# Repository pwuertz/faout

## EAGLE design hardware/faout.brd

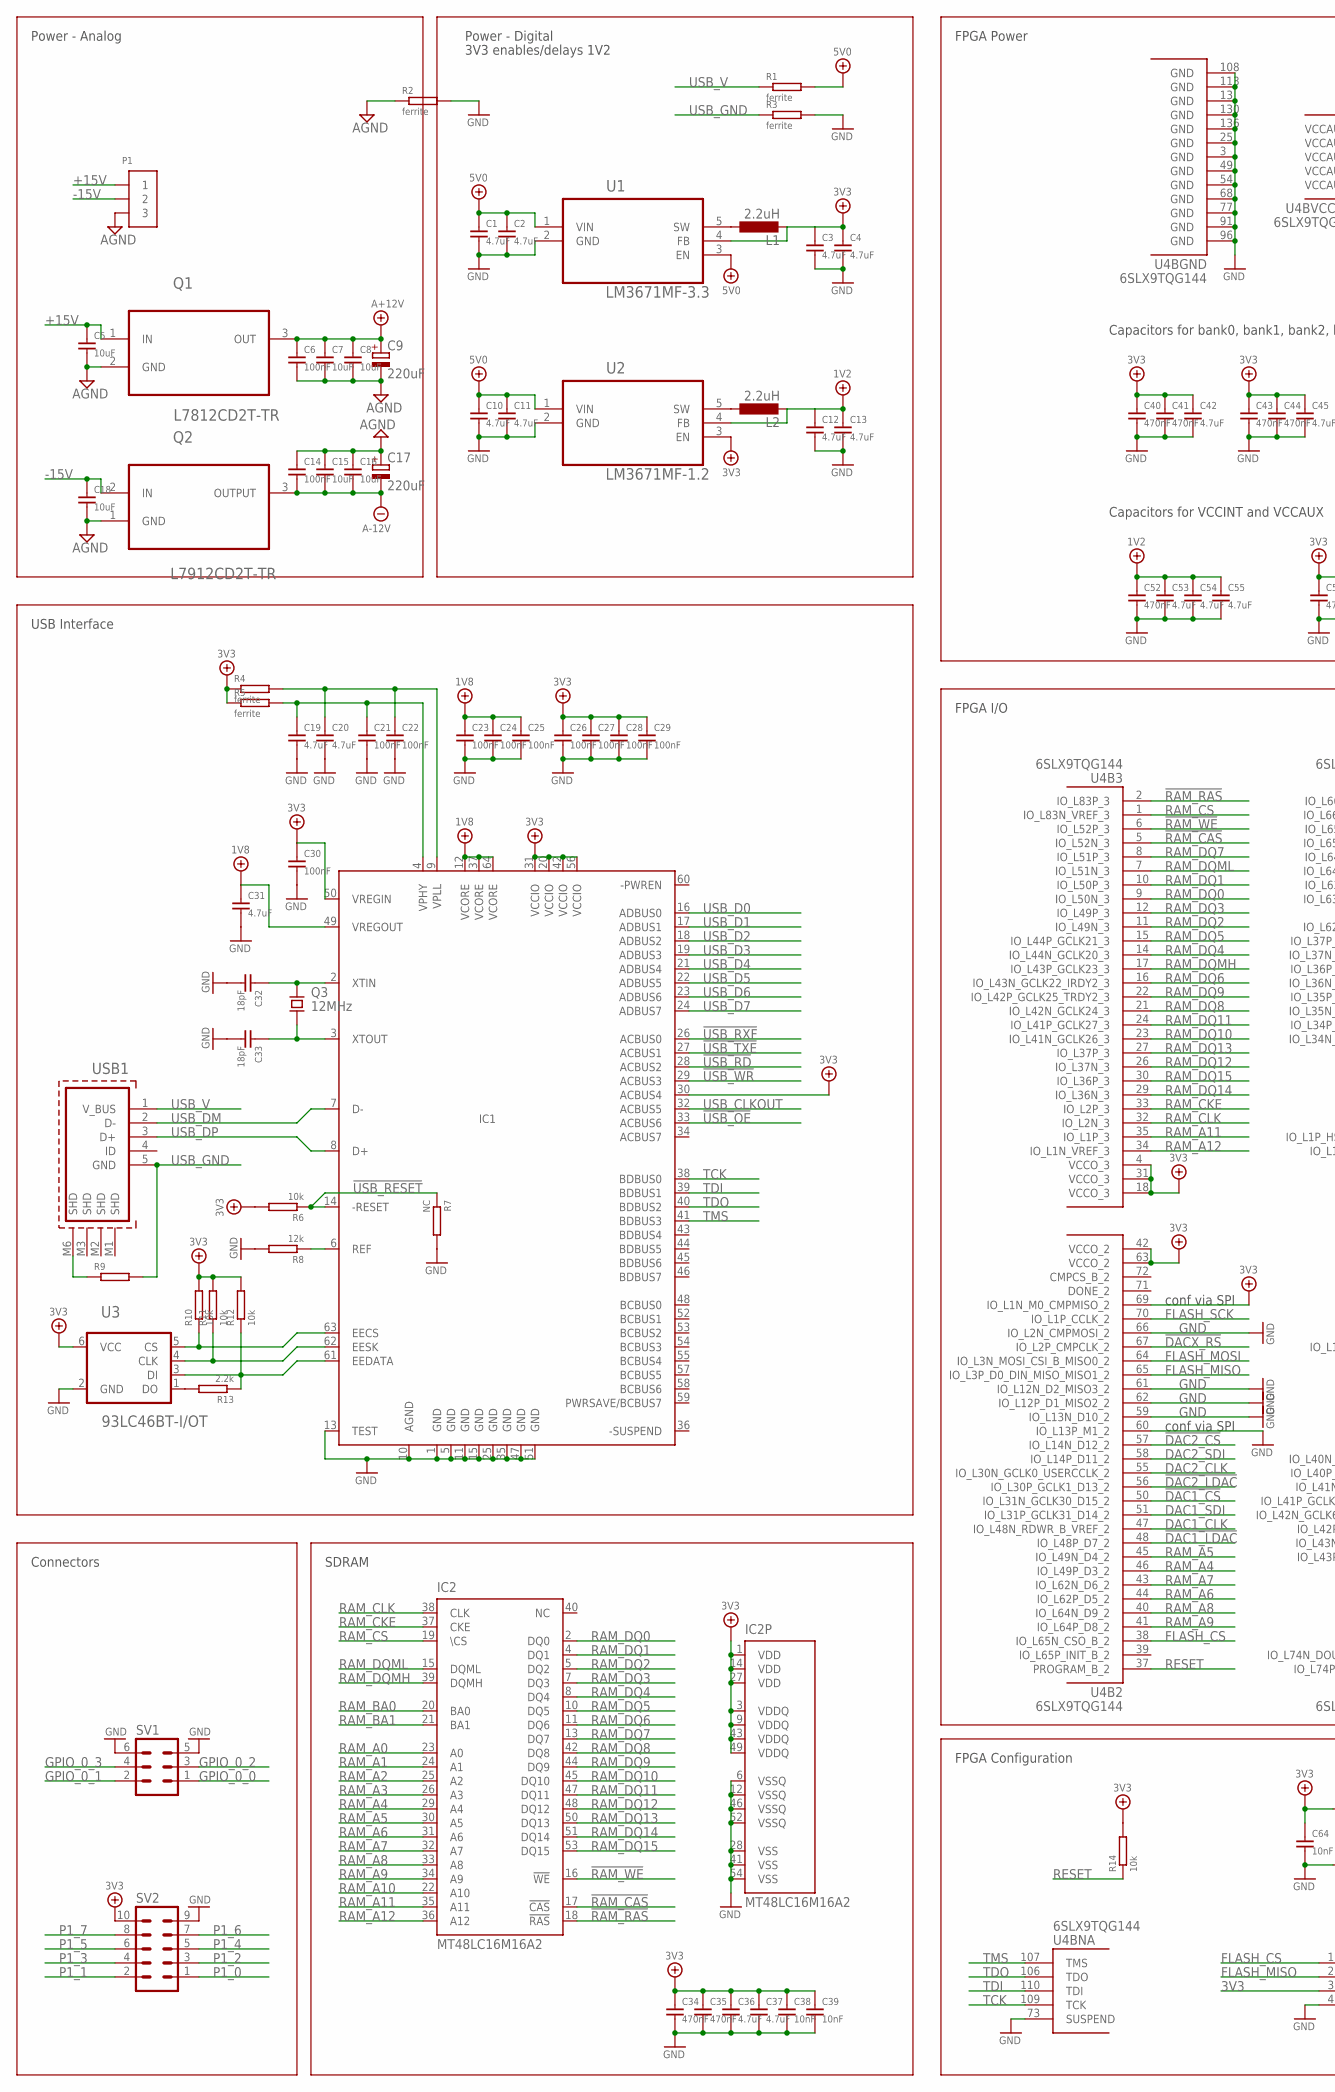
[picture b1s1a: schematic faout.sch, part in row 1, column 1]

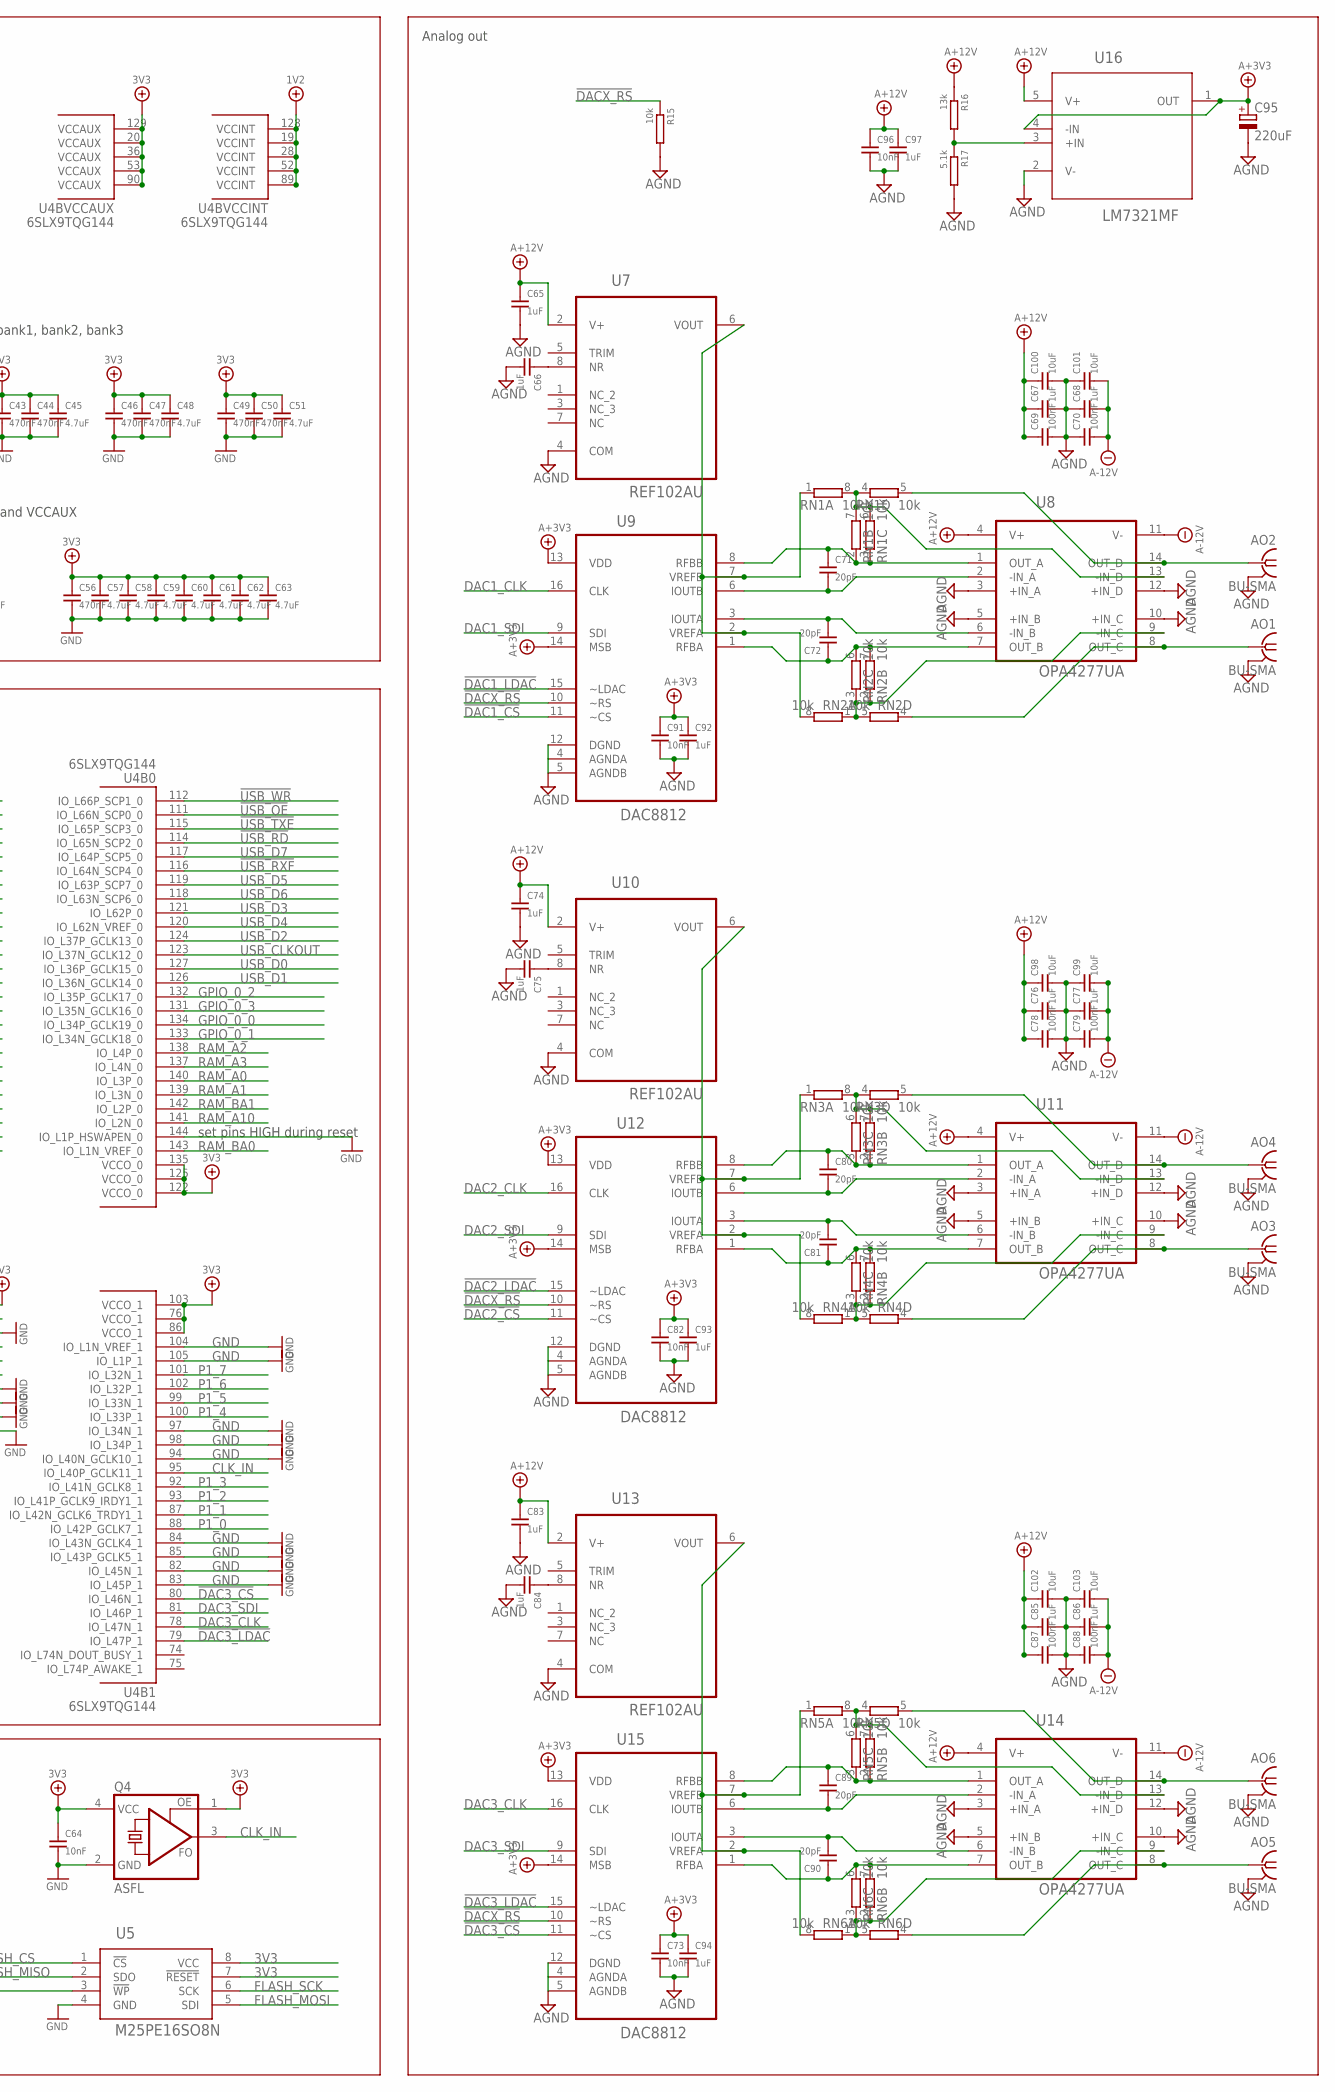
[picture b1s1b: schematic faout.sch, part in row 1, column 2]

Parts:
AO1, AO2, AO3, AO4, AO5, AO6: BU-SMA; BU-SMA-H
C1, C2, C3, C4, C10, C11, C12, C13, C19, C20, C31, C36, C37, C42, C45, C48, C51, C53, C54, C55, C57, C58, C59, C60, C61, C62, C63: 4.7uF; R0603
C5, C7, C8, C15, C16, C18, C98, C99, C100, C101, C102, C103: 10uF; R0805
C6, C14, C21, C22, C23, C24, C25, C26, C27, C28, C29, C30, C69, C70, C78, C79, C87, C88: 100nF; R0603
C9, C17, C95: 220uF; PANASONIC_E
C32, C33: 18pF; R0603
C34, C35, C40, C41, C43, C44, C46, C47, C49, C50, C52, C56: 470nF; R0603
C38, C39, C64, C73, C82, C91, C96: 10nF; R0603
C65, C66, C67, C68, C74, C75, C76, C77, C83, C84, C85, C86, C92, C93, C94, C97: 1uF; R0603
C71, C72, C80, C81, C89, C90: 20pF; R0603
IC1: FT2232HL; TQFP64-12X12
IC2: MT48LC16M16A2; TSOP54-400
L1, L2: 2.2uH; L5038P
P1: TE_CONN_MTE_HEADER3R; TE_CONN_MTE_HEADER3_R
Q1: L7812CD2T-TR; TO254P1524X460-3N
Q2: L7912CD2T-TR; TO254P1524X460-3N
Q3: 12MHz; TXC_QUARTZ_7A
Q4: ASFL; ASF
R1, R2, R3: ferrite; R1206
R4, R5: ferrite; R0603
R6, R10, R11, R12, R14, R15: 10k; R0603
R7: NC; R0603
R8: 12k; R0603
R9: R_EU0603; R0603
R13: 2.2k; R0603
R16: 13k; R0603
R17: 5.1k; R0603
RN1, RN2, RN3, RN4, RN5, RN6: 10k; EXBV8V
SV1: ML6L
SV2: ML10
U1: LM3671MF-3.3; SOT95P284X122-5N
U2: LM3671MF-1.2; SOT95P284X122-5N
U3: 93LC46BT-I/OT; SOT95P280X145-6N
U4: 6SLX9TQG144; TQ144
U5: M25PE16SO8N; SOIC127P600X175-8N
U7, U10, U13: REF102AU; SOIC127P600X175-8N
U8, U11, U14: OPA4277UA; SOIC127P600X175-14N
U9, U12, U15: DAC8812; SOP65P640X120-16N
U16: LM7321MF; SOT95P300X120-5N
USB1: MOLEX_USB_105017-0001; MOLEX_105017-0001

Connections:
1V2: C12.1, C13.1, C52.1, C53.1, C54.1, C55.1, L2.2, U2.4 (FB), U4.19 (VCCINT), U4.28 (VCCINT), U4.52 (VCCINT), U4.89 (VCCINT), U4.128 (VCCINT)
1V8: C23.1, C24.1, C25.1, C31.1, IC1.12 (VCORE), IC1.37 (VCORE), IC1.49 (VREGOUT), IC1.64 (VCORE)
3V3: C3.1, C4.1, C26.1, C27.1, C28.1, C29.1, C30.1, C34.1, C35.1, C36.1, C37.1, C38.1, C39.1, C40.1, C41.1, C42.1, C43.1, C44.1, C45.1, C46.1, C47.1, C48.1, C49.1, C50.1, C51.1, C56.1, C57.1, C58.1, C59.1, C60.1, C61.1, C62.1, C63.1, C64.1, IC1.20 (VCCIO), IC1.30 (ACBUS4), IC1.31 (VCCIO), IC1.42 (VCCIO), IC1.50 (VREGIN), IC1.56 (VCCIO), IC2.1 (VDD), IC2.3 (VDDQ), IC2.9 (VDDQ), IC2.14 (VDD), IC2.27 (VDD), IC2.43 (VDDQ), IC2.49 (VDDQ), L1.2, Q4.1 (OE), Q4.4 (VCC), R4.1, R5.1, R6.2, R10.2, R11.2, R12.2, R14.2, SV2.10, U1.4 (FB), U2.3 (EN), U3.6 (VCC), U4.4 (VCCO_3), U4.18 (VCCO_3), U4.20 (VCCAUX), U4.31 (VCCO_3), U4.36 (VCCAUX), U4.42 (VCCO_2), U4.53 (VCCAUX), U4.63 (VCCO_2), U4.69 (IO_L1N_M0_CMPMISO_2), U4.76 (VCCO_1), U4.86 (VCCO_1), U4.90 (VCCAUX), U4.103 (VCCO_1), U4.122 (VCCO_0), U4.125 (VCCO_0), U4.129 (VCCAUX), U4.135 (VCCO_0), U5.3 (!WP), U5.7 (!RESET), U5.8 (VCC)
5V0: C1.1, C2.1, C10.1, C11.1, R1.2, U1.1 (VIN), U1.3 (EN), U2.1 (VIN)
!DAC1_CS: U4.50 (IO_L31N_GCLK30_D15_2), U9.11 (~CS)
!DAC1_LDAC: U4.48 (IO_L48P_D7_2), U9.15 (~LDAC)
!DAC2_CS: U4.57 (IO_L14N_D12_2), U12.11 (~CS)
!DAC2_LDAC: U4.56 (IO_L30P_GCLK1_D13_2), U12.15 (~LDAC)
!DAC3_CS: U4.80 (IO_L46N_1), U15.11 (~CS)
!DAC3_LDAC: U4.79 (IO_L47P_1), U15.15 (~LDAC)
!DACX_RS: R15.1, U4.67 (IO_L2P_CMPCLK_2), U9.10 (~RS), U12.10 (~RS), U15.10 (~RS)
!RAM_CAS: IC2.17 (!CAS), U4.5 (IO_L52N_3)
!RAM_RAS: IC2.18 (!RAS), U4.2 (IO_L83P_3)
!RAM_WE: IC2.16 (!WE), U4.6 (IO_L52P_3)
!USB_OE: IC1.33 (ACBUS6), U4.111 (IO_L66N_SCP0_0)
!USB_RD: IC1.28 (ACBUS2), U4.114 (IO_L65N_SCP2_0)
!USB_RESET: IC1.14 (-RESET), R6.1, R7.1
!USB_RXF: IC1.26 (ACBUS0), U4.116 (IO_L64N_SCP4_0)
!USB_TXE: IC1.27 (ACBUS1), U4.115 (IO_L65P_SCP3_0)
!USB_WR: IC1.29 (ACBUS3), U4.112 (IO_L66P_SCP1_0)
+15V: C5.1, P1.P$1 (1), Q1.1 (IN)
-15V: C18.1, P1.P$2 (2), Q2.2 (IN)
A+3V3: C73.1, C82.1, C91.1, C92.1, C93.1, C94.1, C95.+, U9.13 (VDD), U9.14 (MSB), U12.13 (VDD), U12.14 (MSB), U15.13 (VDD), U15.14 (MSB), U16.1 (OUT), U16.4 (-IN)
A+12V: C6.1, C7.1, C8.1, C9.+, C65.1, C67.1, C69.1, C74.1, C76.1, C78.1, C83.1, C85.1, C87.1, C96.1, C97.1, C98.1, C100.1, C102.1, Q1.3 (OUT), R16.1, U7.2 (V+), U8.4 (V+), U10.2 (V+), U11.4 (V+), U13.2 (V+), U14.4 (V+), U16.5 (V+)
A-12V: C14.2, C15.2, C16.2, C17.-, C68.2, C70.2, C77.2, C79.2, C86.2, C88.2, C99.2, C101.2, C103.2, Q2.3 (OUTPUT), U8.11 (V-), U11.11 (V-), U14.11 (V-)
AGND: AO1.2, AO1.3 (2), AO1.4 (2), AO1.5 (2), AO2.2, AO2.3 (2), AO2.4 (2), AO2.5 (2), AO3.2, AO3.3 (2), AO3.4 (2), AO3.5 (2), AO4.2, AO4.3 (2), AO4.4 (2), AO4.5 (2), AO5.2, AO5.3 (2), AO5.4 (2), AO5.5 (2), AO6.2, AO6.3 (2), AO6.4 (2), AO6.5 (2), C5.2, C6.2, C7.2, C8.2, C9.-, C14.1, C15.1, C16.1, C17.+, C18.2, C65.2, C66.2, C67.2, C68.1, C69.2, C70.1, C73.2, C74.2, C75.2, C76.2, C77.1, C78.2, C79.1, C82.2, C83.2, C84.2, C85.2, C86.1, C87.2, C88.1, C91.2, C92.2, C93.2, C94.2, C95.-, C96.2, C97.2, C98.2, C99.1, C100.2, C101.1, C102.2, C103.1, P1.P$3 (3), Q1.2 (GND), Q2.1 (GND), R2.1, R15.2, R17.2, U7.4 (COM), U8.3 (+IN_A), U8.5 (+IN_B), U8.10 (+IN_C), U8.12 (+IN_D), U9.4 (AGNDA), U9.5 (AGNDB), U9.12 (DGND), U10.4 (COM), U11.3 (+IN_A), U11.5 (+IN_B), U11.10 (+IN_C), U11.12 (+IN_D), U12.4 (AGNDA), U12.5 (AGNDB), U12.12 (DGND), U13.4 (COM), U14.3 (+IN_A), U14.5 (+IN_B), U14.10 (+IN_C), U14.12 (+IN_D), U15.4 (AGNDA), U15.5 (AGNDB), U15.12 (DGND), U16.2 (V-)
CLK_IN: Q4.3 (FO), U4.95 (IO_L40P_GCLK11_1)
DAC1_CLK: U4.47 (IO_L48N_RDWR_B_VREF_2), U9.16 (CLK)
DAC1_IOUTA: C72.2, U8.6 (-IN_B), U9.3 (IOUTA)
DAC1_IOUTB: C71.2, U8.2 (-IN_A), U9.6 (IOUTB)
DAC1_RFBA: C72.1, RN2.6 (2), RN2.7 (2), U8.7 (OUT_B), U9.1 (RFBA)
DAC1_RFBB: C71.1, RN1.2 (1), RN1.3 (1), U8.1 (OUT_A), U9.8 (RFBB)
DAC1_SDI: U4.51 (IO_L31P_GCLK31_D14_2), U9.9 (SDI)
DAC1_VOUTA: AO1.1, RN2.4 (1), U8.8 (OUT_C)
DAC1_VOUTB: AO2.1, RN1.5 (2), U8.14 (OUT_D)
DAC1_VREF: RN1.1, RN2.8 (2), U7.6 (VOUT), U9.2 (VREFA), U9.7 (VREFB)
DAC2_CLK: U4.55 (IO_L30N_GCLK0_USERCCLK_2), U12.16 (CLK)
DAC2_IOUTA: C81.2, U11.6 (-IN_B), U12.3 (IOUTA)
DAC2_IOUTB: C80.2, U11.2 (-IN_A), U12.6 (IOUTB)
DAC2_RFBA: C81.1, RN4.6 (2), RN4.7 (2), U11.7 (OUT_B), U12.1 (RFBA)
DAC2_RFBB: C80.1, RN3.2 (1), RN3.3 (1), U11.1 (OUT_A), U12.8 (RFBB)
DAC2_SDI: U4.58 (IO_L14P_D11_2), U12.9 (SDI)
DAC2_VOUTA: AO3.1, RN4.4 (1), U11.8 (OUT_C)
DAC2_VOUTB: AO4.1, RN3.5 (2), U11.14 (OUT_D)
DAC2_VREF: RN3.1, RN4.8 (2), U10.6 (VOUT), U12.2 (VREFA), U12.7 (VREFB)
DAC3_CLK: U4.78 (IO_L47N_1), U15.16 (CLK)
DAC3_IOUTA: C90.2, U14.6 (-IN_B), U15.3 (IOUTA)
DAC3_IOUTB: C89.2, U14.2 (-IN_A), U15.6 (IOUTB)
DAC3_RFBA: C90.1, RN6.6 (2), RN6.7 (2), U14.7 (OUT_B), U15.1 (RFBA)
DAC3_RFBB: C89.1, RN5.2 (1), RN5.3 (1), U14.1 (OUT_A), U15.8 (RFBB)
DAC3_SDI: U4.81 (IO_L46P_1), U15.9 (SDI)
DAC3_VOUTA: AO5.1, RN6.4 (1), U14.8 (OUT_C)
DAC3_VOUTB: AO6.1, RN5.5 (2), U14.14 (OUT_D)
DAC3_VREF: RN5.1, RN6.8 (2), U13.6 (VOUT), U15.2 (VREFA), U15.7 (VREFB)
EECS: IC1.63 (EECS), R10.1, U3.5 (CS)
EEDATA: IC1.61 (EEDATA), R12.1, R13.1, U3.3 (DI)
EESK: IC1.62 (EESK), R11.1, U3.4 (CLK)
FLASH_CS: U4.38 (IO_L65N_CSO_B_2), U5.1 (!CS)
FLASH_MISO: U4.65 (IO_L3P_D0_DIN_MISO_MISO1_2), U5.2 (SDO)
FLASH_MOSI: U4.64 (IO_L3N_MOSI_CSI_B_MISO0_2), U5.5 (SDI)
FLASH_SCK: U4.70 (IO_L1P_CCLK_2), U5.6 (SCK)
GND: C1.2, C2.2, C3.2, C4.2, C10.2, C11.2, C12.2, C13.2, C19.2, C20.2, C21.2, C22.2, C23.2, C24.2, C25.2, C26.2, C27.2, C28.2, C29.2, C30.2, C31.2, C32.2, C33.2, C34.2, C35.2, C36.2, C37.2, C38.2, C39.2, C40.2, C41.2, C42.2, C43.2, C44.2, C45.2, C46.2, C47.2, C48.2, C49.2, C50.2, C51.2, C52.2, C53.2, C54.2, C55.2, C56.2, C57.2, C58.2, C59.2, C60.2, C61.2, C62.2, C63.2, C64.2, IC1.1 (GND), IC1.5 (GND), IC1.10 (AGND), IC1.11 (GND), IC1.13 (TEST), IC1.15 (GND), IC1.25 (GND), IC1.35 (GND), IC1.47 (GND), IC1.51 (GND), IC2.6 (VSSQ), IC2.12 (VSSQ), IC2.28 (VSS), IC2.41 (VSS), IC2.46 (VSSQ), IC2.52 (VSSQ), IC2.54 (VSS), Q4.2 (GND), R2.2, R3.2, R7.2, R8.2, SV1.5, SV1.6, SV2.9, U1.2 (GND), U2.2 (GND), U3.2 (GND), U4.3 (GND), U4.13 (GND), U4.25 (GND), U4.49 (GND), U4.54 (GND), U4.59 (IO_L13N_D10_2), U4.60 (IO_L13P_M1_2), U4.61 (IO_L12N_D2_MISO3_2), U4.62 (IO_L12P_D1_MISO2_2), U4.66 (IO_L2N_CMPMOSI_2), U4.68 (GND), U4.73 (SUSPEND), U4.77 (GND), U4.82 (IO_L45N_1), U4.83 (IO_L45P_1), U4.84 (IO_L43N_GCLK4_1), U4.85 (IO_L43P_GCLK5_1), U4.91 (GND), U4.94 (IO_L40N_GCLK10_1), U4.96 (GND), U4.97 (IO_L34N_1), U4.98 (IO_L34P_1), U4.104 (IO_L1N_VREF_1), U4.105 (IO_L1P_1), U4.108 (GND), U4.113 (GND), U4.130 (GND), U4.136 (GND), U4.144 (IO_L1P_HSWAPEN_0), U5.4 (GND)
GPIO_0_0: SV1.1, U4.134 (IO_L34P_GCLK19_0)
GPIO_0_1: SV1.2, U4.133 (IO_L34N_GCLK18_0)
GPIO_0_2: SV1.3, U4.132 (IO_L35P_GCLK17_0)
GPIO_0_3: SV1.4, U4.131 (IO_L35N_GCLK16_0)
unnamed: C32.1, IC1.2 (XTIN), Q3.1
unnamed: C33.1, IC1.3 (XTOUT), Q3.2
unnamed: C66.1, U7.8 (NR)
unnamed: C19.1, C21.1, IC1.4 (VPHY), R5.2
unnamed: R13.2, U3.1 (DO)
unnamed: C20.1, C22.1, IC1.9 (VPLL), R4.2
unnamed: RN2.1, RN2.2 (1), RN2.3 (1), RN2.5 (2), U8.9 (-IN_C)
unnamed: RN4.1, RN4.2 (1), RN4.3 (1), RN4.5 (2), U11.9 (-IN_C)
unnamed: RN5.4 (1), RN5.6 (2), RN5.7 (2), RN5.8 (2), U14.13 (-IN_D)
unnamed: C75.1, U10.8 (NR)
unnamed: C84.1, U13.8 (NR)
unnamed: R16.2, R17.1, U16.3 (+IN)
unnamed: RN6.1, RN6.2 (1), RN6.3 (1), RN6.5 (2), U14.9 (-IN_C)
unnamed: R9.1, USB1.M6 (SHD)
unnamed: RN1.4 (1), RN1.6 (2), RN1.7 (2), RN1.8 (2), U8.13 (-IN_D)
unnamed: RN3.4 (1), RN3.6 (2), RN3.7 (2), RN3.8 (2), U11.13 (-IN_D)
unnamed: L1.1, U1.5 (SW)
unnamed: L2.1, U2.5 (SW)
P1_0: SV2.1, U4.88 (IO_L42P_GCLK7_1)
P1_1: SV2.2, U4.87 (IO_L42N_GCLK6_TRDY1_1)
P1_2: SV2.3, U4.93 (IO_L41P_GCLK9_IRDY1_1)
P1_3: SV2.4, U4.92 (IO_L41N_GCLK8_1)
P1_4: SV2.5, U4.100 (IO_L33P_1)
P1_5: SV2.6, U4.99 (IO_L33N_1)
P1_6: SV2.7, U4.102 (IO_L32P_1)
P1_7: SV2.8, U4.101 (IO_L32N_1)
RAM_A0: IC2.23 (A0), U4.140 (IO_L3P_0)
RAM_A1: IC2.24 (A1), U4.139 (IO_L3N_0)
RAM_A2: IC2.25 (A2), U4.138 (IO_L4P_0)
RAM_A3: IC2.26 (A3), U4.137 (IO_L4N_0)
RAM_A4: IC2.29 (A4), U4.46 (IO_L49P_D3_2)
RAM_A5: IC2.30 (A5), U4.45 (IO_L49N_D4_2)
RAM_A6: IC2.31 (A6), U4.44 (IO_L62P_D5_2)
RAM_A7: IC2.32 (A7), U4.43 (IO_L62N_D6_2)
RAM_A8: IC2.33 (A8), U4.40 (IO_L64N_D9_2)
RAM_A9: IC2.34 (A9), U4.41 (IO_L64P_D8_2)
RAM_A10: IC2.22 (A10), U4.141 (IO_L2N_0)
RAM_A11: IC2.35 (A11), U4.35 (IO_L1P_3)
RAM_A12: IC2.36 (A12), U4.34 (IO_L1N_VREF_3)
RAM_BA0: IC2.20 (BA0), U4.143 (IO_L1N_VREF_0)
RAM_BA1: IC2.21 (BA1), U4.142 (IO_L2P_0)
RAM_CKE: IC2.37 (CKE), U4.33 (IO_L2P_3)
RAM_CLK: IC2.38 (CLK), U4.32 (IO_L2N_3)
RAM_CS: IC2.19 (\CS), U4.1 (IO_L83N_VREF_3)
RAM_DQ0: IC2.2 (DQ0), U4.9 (IO_L50N_3)
RAM_DQ1: IC2.4 (DQ1), U4.10 (IO_L50P_3)
RAM_DQ2: IC2.5 (DQ2), U4.11 (IO_L49N_3)
RAM_DQ3: IC2.7 (DQ3), U4.12 (IO_L49P_3)
RAM_DQ4: IC2.8 (DQ4), U4.14 (IO_L44N_GCLK20_3)
RAM_DQ5: IC2.10 (DQ5), U4.15 (IO_L44P_GCLK21_3)
RAM_DQ6: IC2.11 (DQ6), U4.16 (IO_L43N_GCLK22_IRDY2_3)
RAM_DQ7: IC2.13 (DQ7), U4.8 (IO_L51P_3)
RAM_DQ8: IC2.42 (DQ8), U4.21 (IO_L42N_GCLK24_3)
RAM_DQ9: IC2.44 (DQ9), U4.22 (IO_L42P_GCLK25_TRDY2_3)
RAM_DQ10: IC2.45 (DQ10), U4.23 (IO_L41N_GCLK26_3)
RAM_DQ11: IC2.47 (DQ11), U4.24 (IO_L41P_GCLK27_3)
RAM_DQ12: IC2.48 (DQ12), U4.26 (IO_L37N_3)
RAM_DQ13: IC2.50 (DQ13), U4.27 (IO_L37P_3)
RAM_DQ14: IC2.51 (DQ14), U4.29 (IO_L36N_3)
RAM_DQ15: IC2.53 (DQ15), U4.30 (IO_L36P_3)
RAM_DQMH: IC2.39 (DQMH), U4.17 (IO_L43P_GCLK23_3)
RAM_DQML: IC2.15 (DQML), U4.7 (IO_L51N_3)
RESET: R14.1, U4.37 (PROGRAM_B_2)
TCK: IC1.38 (BDBUS0), U4.109 (TCK)
TDI: IC1.39 (BDBUS1), U4.110 (TDI)
TDO: IC1.40 (BDBUS2), U4.106 (TDO)
TMS: IC1.41 (BDBUS3), U4.107 (TMS)
USB_CLKOUT: IC1.32 (ACBUS5), U4.123 (IO_L37N_GCLK12_0)
USB_D0: IC1.16 (ADBUS0), U4.127 (IO_L36P_GCLK15_0)
USB_D1: IC1.17 (ADBUS1), U4.126 (IO_L36N_GCLK14_0)
USB_D2: IC1.18 (ADBUS2), U4.124 (IO_L37P_GCLK13_0)
USB_D3: IC1.19 (ADBUS3), U4.121 (IO_L62P_0)
USB_D4: IC1.21 (ADBUS4), U4.120 (IO_L62N_VREF_0)
USB_D5: IC1.22 (ADBUS5), U4.119 (IO_L63P_SCP7_0)
USB_D6: IC1.23 (ADBUS6), U4.118 (IO_L63N_SCP6_0)
USB_D7: IC1.24 (ADBUS7), U4.117 (IO_L64P_SCP5_0)
USB_DM: IC1.7 (D-), USB1.2 (D-)
USB_DP: IC1.8 (D+), USB1.3 (D+)
USB_GND: R3.1, R9.2, USB1.5 (GND)
USB_REF: IC1.6 (REF), R8.1
USB_V: R1.1, USB1.1 (V_BUS)

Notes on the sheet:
3V3 enables/delays 1V2
Capacitors for bank0, bank1, bank2, bank3
Capacitors for VCCINT and VCCAUX
set pins HIGH during reset
conf via SPI
SDRAM
FPGA Power
FPGA I/O
FPGA Configuration
USB Interface
Power - Digital
Analog out
Power - Analog
Connectors

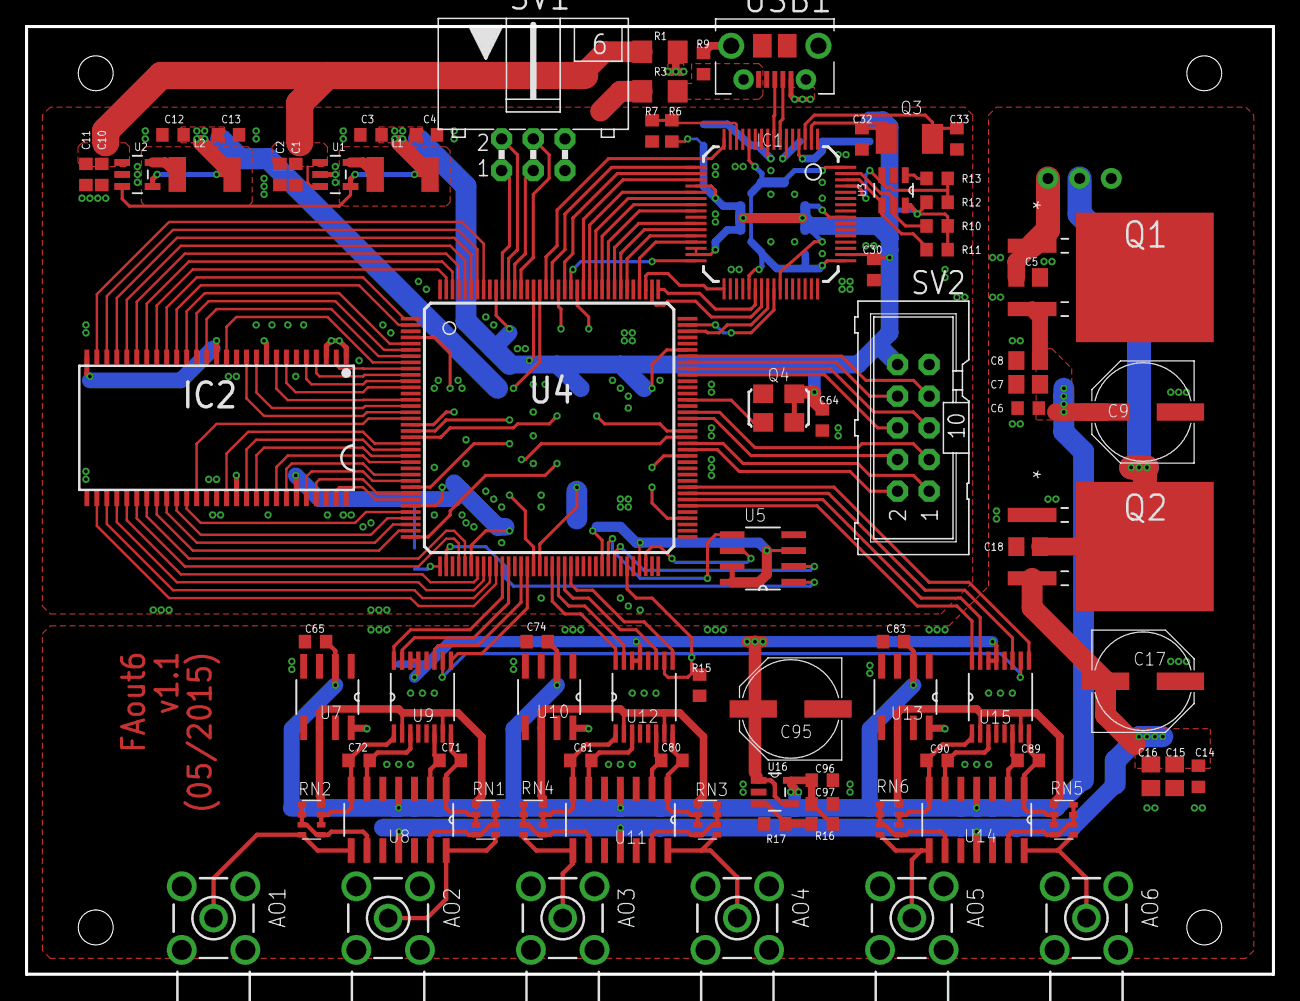
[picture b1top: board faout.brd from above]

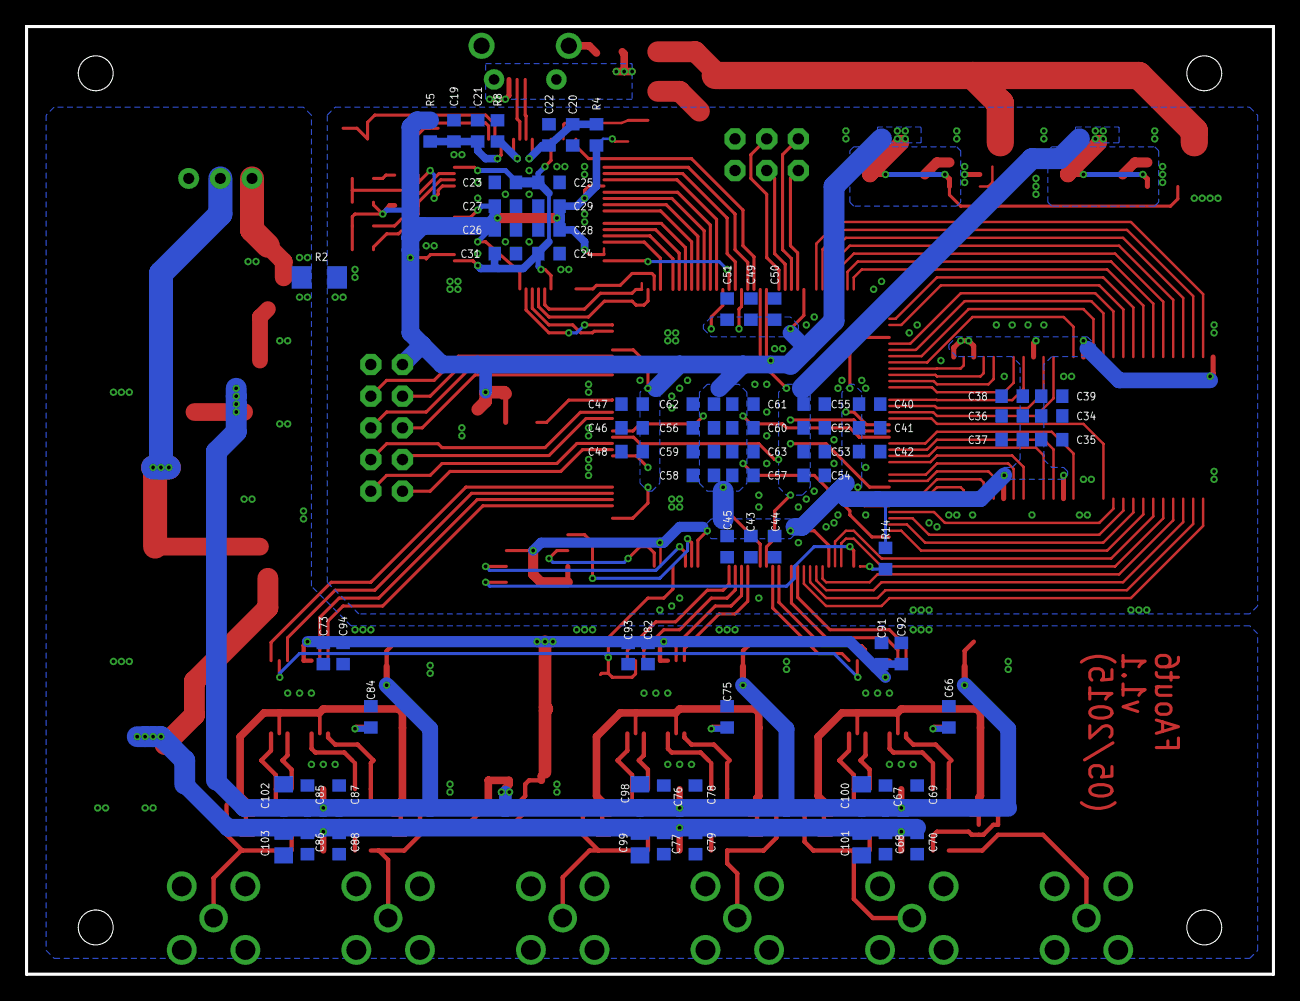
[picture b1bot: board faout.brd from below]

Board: 2 copper layers, 100.0 x 76.0 mm, 159 parts (74 on the bottom side), 147 nets.

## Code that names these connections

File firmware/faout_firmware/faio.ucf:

## main oscillator
NET "clk_osc"     LOC="P95" | IOSTANDARD="LVCMOS33" | TNM_NET="clk_osc";
TIMESPEC TS_clk_osc = PERIOD clk_osc 50 MHz;

## buttons
NET "btn<0>"     LOC="P61"  | IOSTANDARD="LVCMOS33";
NET "btn<1>"     LOC="P62"  | IOSTANDARD="LVCMOS33";
NET "btn<2>"     LOC="P66"  | IOSTANDARD="LVCMOS33";

## leds
NET "led<0>"        LOC="P80"  | IOSTANDARD="LVCMOS33";
NET "led<1>"        LOC="P79"  | IOSTANDARD="LVCMOS33";
NET "led<2>"        LOC="P78"  | IOSTANDARD="LVCMOS33";
NET "led<3>"        LOC="P112" | IOSTANDARD="LVCMOS33";
NET "led<4>"        LOC="P111" | IOSTANDARD="LVCMOS33";

## display
NET "disp_seg<0>"   LOC="P50"  | IOSTANDARD="LVCMOS33";
NET "disp_seg<1>"   LOC="P48"  | IOSTANDARD="LVCMOS33";
NET "disp_seg<2>"   LOC="P56"  | IOSTANDARD="LVCMOS33";
NET "disp_seg<3>"   LOC="P55"  | IOSTANDARD="LVCMOS33";
NET "disp_seg<4>"   LOC="P57"  | IOSTANDARD="LVCMOS33";
NET "disp_seg<5>"   LOC="P51"  | IOSTANDARD="LVCMOS33";
NET "disp_seg<6>"   LOC="P47"  | IOSTANDARD="LVCMOS33";
NET "disp_seg<5>"   LOC="P51"  | IOSTANDARD="LVCMOS33";
NET "disp_seg<6>"   LOC="P47"  | IOSTANDARD="LVCMOS33";
NET "disp_en<0>"    LOC="P58"  | IOSTANDARD="LVCMOS33";
NET "disp_en<1>"    LOC="P59"  | IOSTANDARD="LVCMOS33";

## port1
NET "clk_ext"        LOC="P84"  | IOSTANDARD="LVCMOS33" | TNM_NET="clk_ext";
TIMESPEC TS_clk_ext = PERIOD clk_ext 10 MHz;
NET "P1_1"           LOC="P83"  | IOSTANDARD="LVCMOS33";
NET "P1_2"           LOC="P82"  | IOSTANDARD="LVCMOS33";
#NET "P1<3>"         LOC="P81"  | IOSTANDARD="LVCMOS33";

## sdram
NET "SDRAM_CKE"       LOC="P33"  | IOSTANDARD="LVCMOS33";
NET "SDRAM_CLK"       LOC="P32"  | IOSTANDARD="LVCMOS33";
NET "SDRAM_RAS"       LOC="P2"   | IOSTANDARD="LVCMOS33";
NET "SDRAM_CAS"       LOC="P5"   | IOSTANDARD="LVCMOS33";
NET "SDRAM_WE"        LOC="P6"   | IOSTANDARD="LVCMOS33";
NET "SDRAM_CS"        LOC="P1"   | IOSTANDARD="LVCMOS33";
NET "SDRAM_A<0>"      LOC="P140" | IOSTANDARD="LVCMOS33";
NET "SDRAM_A<1>"      LOC="P139" | IOSTANDARD="LVCMOS33";
NET "SDRAM_A<2>"      LOC="P138" | IOSTANDARD="LVCMOS33";
NET "SDRAM_A<3>"      LOC="P137" | IOSTANDARD="LVCMOS33";
NET "SDRAM_A<4>"      LOC="P46"  | IOSTANDARD="LVCMOS33";
NET "SDRAM_A<5>"      LOC="P45"  | IOSTANDARD="LVCMOS33";
NET "SDRAM_A<6>"      LOC="P44"  | IOSTANDARD="LVCMOS33";
NET "SDRAM_A<7>"      LOC="P43"  | IOSTANDARD="LVCMOS33";
NET "SDRAM_A<8>"      LOC="P41"  | IOSTANDARD="LVCMOS33";
NET "SDRAM_A<9>"      LOC="P40"  | IOSTANDARD="LVCMOS33";
NET "SDRAM_A<10>"     LOC="P141" | IOSTANDARD="LVCMOS33";
NET "SDRAM_A<11>"     LOC="P35"  | IOSTANDARD="LVCMOS33";
NET "SDRAM_BA<0>"     LOC="P143" | IOSTANDARD="LVCMOS33";
NET "SDRAM_BA<1>"     LOC="P142" | IOSTANDARD="LVCMOS33";
NET "SDRAM_DQ<0>"     LOC="P9"   | IOSTANDARD="LVCMOS33";
NET "SDRAM_DQ<1>"     LOC="P10"  | IOSTANDARD="LVCMOS33";
NET "SDRAM_DQ<2>"     LOC="P11"  | IOSTANDARD="LVCMOS33";
NET "SDRAM_DQ<3>"     LOC="P12"  | IOSTANDARD="LVCMOS33";
NET "SDRAM_DQ<4>"     LOC="P14"  | IOSTANDARD="LVCMOS33";
NET "SDRAM_DQ<5>"     LOC="P15"  | IOSTANDARD="LVCMOS33";
NET "SDRAM_DQ<6>"     LOC="P16"  | IOSTANDARD="LVCMOS33";
NET "SDRAM_DQ<7>"     LOC="P8"   | IOSTANDARD="LVCMOS33";
NET "SDRAM_DQ<8>"     LOC="P21"  | IOSTANDARD="LVCMOS33";
NET "SDRAM_DQ<9>"     LOC="P22"  | IOSTANDARD="LVCMOS33";
NET "SDRAM_DQ<10>"    LOC="P23"  | IOSTANDARD="LVCMOS33";
NET "SDRAM_DQ<11>"    LOC="P24"  | IOSTANDARD="LVCMOS33";
NET "SDRAM_DQ<12>"    LOC="P26"  | IOSTANDARD="LVCMOS33";
NET "SDRAM_DQ<13>"    LOC="P27"  | IOSTANDARD="LVCMOS33";
NET "SDRAM_DQ<14>"    LOC="P29"  | IOSTANDARD="LVCMOS33";
NET "SDRAM_DQ<15>"    LOC="P30"  | IOSTANDARD="LVCMOS33";
NET "SDRAM_DQM<1>"    LOC="P17"  | IOSTANDARD="LVCMOS33";
NET "SDRAM_DQM<0>"    LOC="P7"   | IOSTANDARD="LVCMOS33";

## usb interface
NET "USB_CLK"       LOC="P123" | IOSTANDARD="LVCMOS33" | TNM_NET = "USB_CLK";
TIMESPEC "TS_USB_CLK" = PERIOD "USB_CLK" 60 MHz HIGH 50%;
OFFSET = IN 7.15ns VALID 9.51 AFTER "USB_CLK" HIGH;
OFFSET = OUT 7.4ns VALID 7.4ns BEFORE "USB_CLK" HIGH; # should be 8ns

NET "USB_OE_N"      LOC="P116" | IOSTANDARD="LVCMOS33";
NET "USB_RD_N"      LOC="P119" | IOSTANDARD="LVCMOS33";
NET "USB_WR_N"      LOC="P118" | IOSTANDARD="LVCMOS33";
NET "USB_RXF_N"     LOC="P121" | IOSTANDARD="LVCMOS33";
NET "USB_TXE_N"     LOC="P120" | IOSTANDARD="LVCMOS33";
NET "USB_D<0>"      LOC="P117" | IOSTANDARD="LVCMOS33";
NET "USB_D<1>"      LOC="P134" | IOSTANDARD="LVCMOS33";
NET "USB_D<2>"      LOC="P133" | IOSTANDARD="LVCMOS33";
NET "USB_D<3>"      LOC="P132" | IOSTANDARD="LVCMOS33";
NET "USB_D<4>"      LOC="P131" | IOSTANDARD="LVCMOS33";
NET "USB_D<5>"      LOC="P127" | IOSTANDARD="LVCMOS33";
NET "USB_D<6>"      LOC="P126" | IOSTANDARD="LVCMOS33";
NET "USB_D<7>"      LOC="P124" | IOSTANDARD="LVCMOS33";

## adc1
#NET "ADC1_SCK"      LOC="P98"  | IOSTANDARD="LVCMOS33";
#NET "ADC1_CNV"      LOC="P100" | IOSTANDARD="LVCMOS33";
#NET "ADC1_SDO"      LOC="P99"  | IOSTANDARD="LVCMOS33";
#NET "ADC1_SDI"      LOC="P97"  | IOSTANDARD="LVCMOS33";

## dac1
NET "DAC1_CLK"      LOC="P93"  | IOSTANDARD="LVCMOS33";
NET "DAC1_CS"       LOC="P94"  | IOSTANDARD="LVCMOS33";
NET "DAC1_SDI"      LOC="P92"  | IOSTANDARD="LVCMOS33";

## dac2
NET "DAC2_CLK"      LOC="P87"  | IOSTANDARD="LVCMOS33";
NET "DAC2_CS"       LOC="P88"  | IOSTANDARD="LVCMOS33";
NET "DAC2_SDI"      LOC="P85"  | IOSTANDARD="LVCMOS33";

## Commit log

2014-05-12 Init repository.
2014-05-16 Begin hardware layout.
2014-05-19 Development of FAout hardware.
2014-05-22 More ADC research.
2014-05-23 Add DAC converters.
2014-05-25 Connected DACs to power and FPGA.
2014-05-26 Add parts for ADC conversion.
2014-05-27 Reroute USB
2014-05-27 Finalize USB and ADC layout.
2014-05-27 Added 7-segment display.
2014-05-28 Finished User IO, create new power supply.
2014-05-29 Finalize design.
2014-05-29 Unify analog regulators.
2014-05-29 Rearrange labels
2014-05-29 Cleanup and last adjustments.
2014-06-02 Fix display orientation and start production.
2014-06-04 Cover vias under USB connector.
2014-06-24 Fix DAC voltage ref oscillations in next board version.
2014-06-24 Datasheet for FTDI Fifo interface.
2014-06-25 Larger SMD pads and optional capacitors.
2014-07-04 Add VHDL components for FAOUT board.
2014-07-05 Initial python client for FTDI communication.
2014-07-05 Working bi-directional FT2232H interface in VHDL and test code.
2014-07-07 Added ignore file.
2014-07-07 Make read/write priority of FT2232 runtime configurable.
2014-07-11 Correct display pattern.
2014-07-11 Add blocking read method.
2014-07-11 Rename SDRAM signals in ucf master file.
2014-07-22 SDRAM controller in VHDL. Implements FIFO behaviour.
2014-07-28 New DAC8811 implementation where internal freq is 2x outgoing freq.
2014-07-28 Remove unused address bit.
2014-07-28 Renaming start signal for DA conversion.
2014-07-29 Rewrite of the interpolation logic. Use FIFO interface, valid flags and stop when empty.
2014-07-30 SDRAM controller propagates pending clear/rewinds via empty/full signals.
2014-08-07 Fix SDRAM empty flag. Change interpolator interface.
2014-08-07 Add more modules and test benches from FPGA firmware design.
2014-08-19 Sample distribute design stalled when FIFO was empty. Fixed.
2014-10-13 Import VHDL code for faout firmware.
2014-10-14 Move external triggers away from P1(0).
2014-10-16 External clock source
2014-10-16 Add support for external clock source.
2014-10-22 WIP: Design 6channel FAOUT prototype.
2014-10-23 WIP: Compress FAOUT-6 layout to 7cm, use space for connectors.
2014-10-24 Add python usb test application.
2014-10-27 Order code corrections and additions.
2014-10-28 Update UCF file for new board layout.
2014-10-28 Implementation of Faout6, DAC8812 and removed non-faout6 modules.
2014-10-30 Cleanup layout.
2014-10-30 Add flash memory datasheet.
2014-10-31 Add xsvf file for flashing board using firmware version 48.
2014-11-05 Fix output channel numbering in firmware.
2014-11-09 Cleanup VHDL project.
2015-01-22 Add sequence-arm command and auto-arm configuration flag.
2015-01-23 Analog power supply with low profile components.
2015-01-23 Rework DAC power supply. Precision resistor arrays for outputs.
2015-01-23 Add and correct Farnell order codes.
2015-02-17 Attempt to fix sequence startup bug in firmware 52.
2015-02-18 Replace old sequencer with a register based packet processor.
2015-02-18 Remove FIFO interface from interpolator and add clk_en feature.
2015-02-18 Add clk_en to dac module.
2015-02-20 Redesign faout firmware for using top level register / new sequencer approach.
2015-02-26 Make sequencer testbench read from and write to text files.
2015-02-27 Fix SDRAM to FIFO transfer. Don't auto-reset sequence on error.
2015-03-02 Replace USB connector. Minor changes for production.
2015-05-05 Modify board for 256Mbit DRAM (MT48LC16M16) compatibility.
2015-05-18 Fix sdram_fifo read resume bug.
2015-05-18 Firmware version 61.
2015-05-18 Import new communication modules from digitizer project.
2015-05-18 Ported faout firmware to new framework.
2015-05-18 Firmware version 62.
2015-06-11 Positioning of part labels.
2016-07-29 Add GPL license and comments
2016-07-29 Fix line endings
2016-07-29 Pick SDRAM resume fix from master
